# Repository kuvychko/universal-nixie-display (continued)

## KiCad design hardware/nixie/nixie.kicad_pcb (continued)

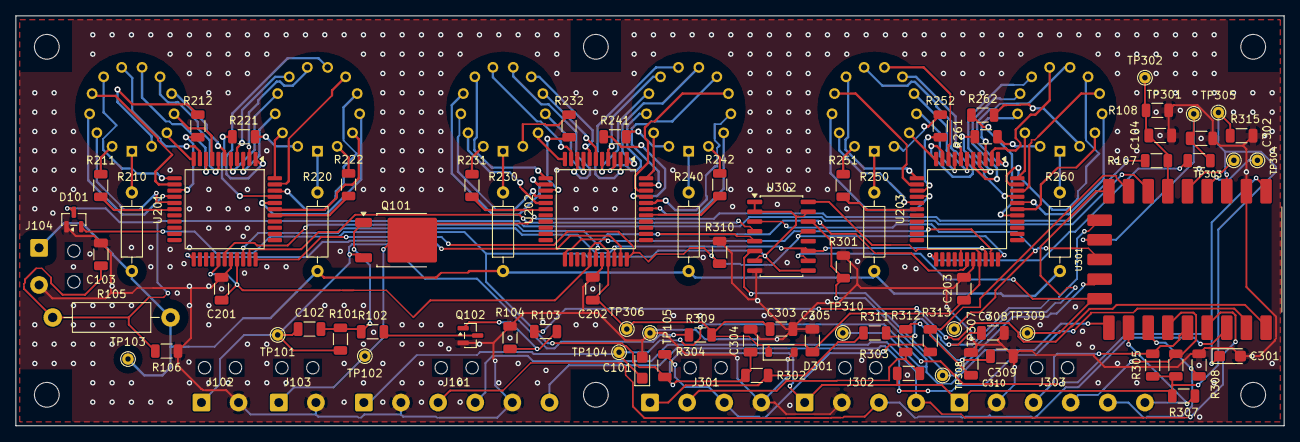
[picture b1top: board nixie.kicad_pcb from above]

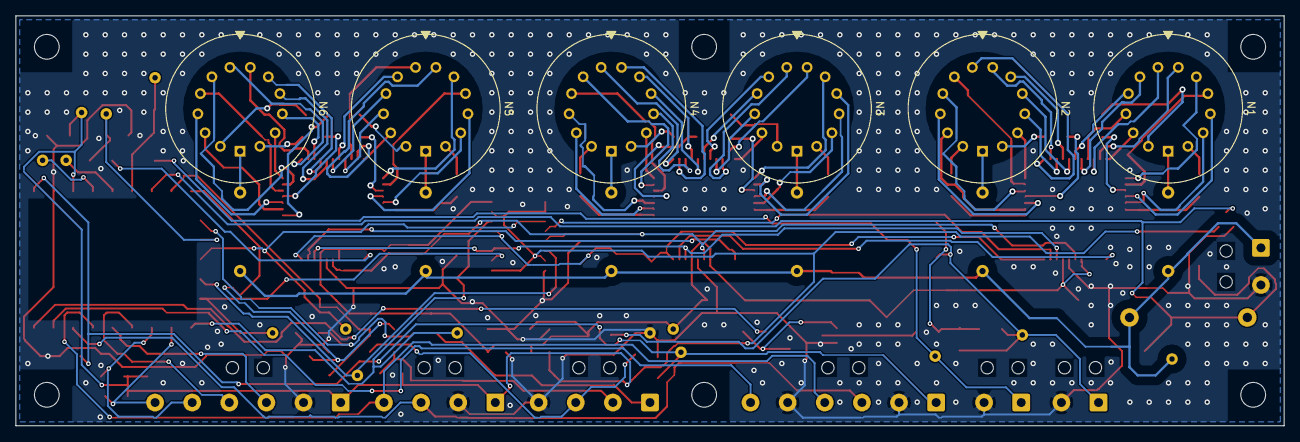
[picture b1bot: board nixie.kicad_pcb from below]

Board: 2 copper layers, 164.0 x 53.0 mm, 106 parts (6 on the bottom side), 130 nets.

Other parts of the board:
H1, H2, H3, H4, H5, H6: MountingHole_3.2mm_M3
TIE_J101, TIE_J102, TIE_J103, TIE_J104, TIE_J301, TIE_J302, TIE_J303: cable tie

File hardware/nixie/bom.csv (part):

Reference,Value,Function,Manufacturer,MPN,Rating,Footprint,Fit
C101,10uF,+5V bulk at the harness landing (user 2026-11-07: as C301),KYOCERA AVX,F911C106MAAAJ6,16 V tantalum,Capacitor_Tantalum_SMD:CP_EIA-3216-18_Kemet-A,
C102,3.3uF,Q101 gate-source: soft turn-on with R101/R102; holds Q101 off on hot-plug,,,25 V X7R,Capacitor_SMD:C_1206_3216Metric,
C103,100nF,NIX_HV_SENSE ADC sampling reservoir (as the dekatron ADC inputs),Yageo,CC1206JPX7R9BB104,50 V X7R,Capacitor_SMD:C_1206_3216Metric,
C104,100nF,NIX12_SENSE ADC sampling reservoir (as the dekatron ADC inputs),Yageo,CC1206JPX7R9BB104,50 V X7R,Capacitor_SMD:C_1206_3216Metric,
C201,0.1uF,U201 VDD bypass,Yageo,CC1206JPX7R9BB104,50 V X7R,Capacitor_SMD:C_1206_3216Metric,
C202,0.1uF,U202 VDD bypass,Yageo,CC1206JPX7R9BB104,50 V X7R,Capacitor_SMD:C_1206_3216Metric,
C203,0.1uF,U203 VDD bypass,Yageo,CC1206JPX7R9BB104,50 V X7R,Capacitor_SMD:C_1206_3216Metric,
C301,10uF,+5V bulk at the module (as dekatron C301),KYOCERA AVX,F911C106MAAAJ6,16 V tantalum,Capacitor_Tantalum_SMD:CP_EIA-3216-18_Kemet-A,
C302,0.1uF,3V3 bypass (as dekatron C302),Yageo,CC1206JPX7R9BB104,50 V X7R,Capacitor_SMD:C_1206_3216Metric,
C303,0.1uF,U302 VDD bypass,Yageo,CC1206JPX7R9BB104,50 V X7R,Capacitor_SMD:C_1206_3216Metric,
C304,0.1uF,U302 VCC bypass,Yageo,CC1206JPX7R9BB104,50 V X7R,Capacitor_SMD:C_1206_3216Metric,
C305,10uF,12 V logic reservoir: shift bursts,,,25 V X7R,Capacitor_SMD:C_1206_3216Metric,
C308,0.01uF,"ENC_A debounce, 0.1 ms with the series 10k (PEC11R suggested filter)",KYOCERA AVX,12063C103JAT2A,25 V X7R,Capacitor_SMD:C_1206_3216Metric,
C309,0.01uF,"ENC_B debounce, 0.1 ms with the series 10k (PEC11R suggested filter)",KYOCERA AVX,12063C103JAT2A,25 V X7R,Capacitor_SMD:C_1206_3216Metric,
C310,0.01uF,"ENC_SW debounce, 0.1 ms with the series 10k (PEC11R suggested filter)",KYOCERA AVX,12063C103JAT2A,25 V X7R,Capacitor_SMD:C_1206_3216Metric,
D101,BAT54S,NIX_HV_SENSE clamp to 3V3 / GND,Taiwan Semiconductor,BAT54S RFG,30 V Schottky pair,Package_TO_SOT_SMD:SOT-23,
D301,MMSZ5243B,12 V logic rail clamp,,MMSZ5243B,"13 V, 500 mW, SOD-123",Diode_SMD:D_SOD-123,
J101,NIX_LV,Harness NIX_LV from the dekatron board (its J302; 5 V behind its ideal diode U104),,,,Connector_Wire:SolderWire-0.5sqmm_1x06_P4.8mm_D0.9mm_OD2.3mm,
J102,12V_IN,"12 V from the dekatron board's NIX_12V (J102, behind its PTC)",,,,Connector_Wire:SolderWire-0.5sqmm_1x02_P4.8mm_D0.9mm_OD2.3mm,
J103,12V_MODULE,Switched 12 V to the Nixie HV module input,,,,Connector_Wire:SolderWire-0.5sqmm_1x02_P4.8mm_D0.9mm_OD2.3mm,
J104,HV_MODULE,Nixie HV module output (~170 V) and its return,,,,Connector_Wire:SolderWire-0.5sqmm_1x02_P4.8mm_D0.9mm_OD2.3mm,
J301,ENCODER,"Harness to the panel-mount encoder (PEC11R): A, B, switch, common C and switch 2",,,,Connector_Wire:SolderWire-0.5sqmm_1x04_P4.8mm_D0.9mm_OD2.3mm,
J302,RTC,Harness to the DS3231 module (ZS-042): jacks on its header by silk name,,,,Connector_Wire:SolderWire-0.5sqmm_1x04_P4.8mm_D0.9mm_OD2.3mm,
J303,WWVB,Harness to the ES100 carrier: jacks on its header by silk name,,,,Connector_Wire:SolderWire-0.5sqmm_1x06_P4.8mm_D0.9mm_OD2.3mm,
N1,IN-14,Tube 1,,IN-14,,nixie:IN-14,
N2,IN-14,Tube 2,,IN-14,,nixie:IN-14,
N3,IN-14,Tube 3,,IN-14,,nixie:IN-14,
N4,IN-14,Tube 4,,IN-14,,nixie:IN-14,
N5,IN-14,Tube 5,,IN-14,,nixie:IN-14,
N6,IN-14,Tube 6,,IN-14,,nixie:IN-14,
Q101,IPD50P04P4L-11,Nixie module 12 V high-side switch with soft start,Infineon,IPD50P04P4L11ATMA2,"-40 V, 17.2 mohm max at VGS -4.5 V, VGS +5/-16 V",Package_TO_SOT_SMD:TO-252-2,
Q102,MMBT3904,Level shifter for Q101's gate,,MMBT3904,40 V NPN,Package_TO_SOT_SMD:SOT-23,
R101,47k,"Q101 gate pull-up: off by default. With R102: VGS -6 V at 12 V, -12 V at the 24 V clamp",,,,Resistor_SMD:R_1206_3216Metric,
R102,47k,Q101 gate series: sets the turn-on ramp with C102,,,,Resistor_SMD:R_1206_3216Metric,
R103,10k,Q102 base (as D8: 3.3 V drive),,,,Resistor_SMD:R_1206_3216Metric,
R104,47k,Q102 base pull-down: switch off while the RP2040 is in reset (D7),,,,Resistor_SMD:R_1206_3216Metric,
R105,1M,"HV monitor divider, upper; bleeder",Yageo,HHV-50FT-52-1M,HHV-50: 0.5 W,Resistor_THT:R_Axial_DIN0411_L9.9mm_D3.6mm_P15.24mm_Horizontal,
R106,12k,"HV monitor divider, lower",Panasonic,ERJ-8ENF1202V,1 %,Resistor_SMD:R_1206_3216Metric,
R107,100k,"+12V_SW sense divider, upper (1.29 V at 12 V)",,,,Resistor_SMD:R_1206_3216Metric,
R108,12k,"+12V_SW sense divider, lower (2.57 V at 24 V)",,,1 %,Resistor_SMD:R_1206_3216Metric,
R210,12k,"Tube 1 anode resistor: (175 V - 145 V) / 2.5 mA, 75 mW",Vishay,MRS25000C1202FRP00,"MRS25: 0.6 W, 350 V, 1 %, 50 ppm/K",Resistor_THT:R_Axial_DIN0207_L6.3mm_D2.5mm_P10.16mm_Horizontal,
R211,150k,"Tube 1 LDP series resistor: starting value, point <= 0.3 mA; check at bring-up",,,,Resistor_SMD:R_1206_3216Metric,
R212,150k,"Tube 1 RDP series resistor: starting value, point <= 0.3 mA; check at bring-up",,,,Resistor_SMD:R_1206_3216Metric,
R220,12k,"Tube 2 anode resistor: (175 V - 145 V) / 2.5 mA, 75 mW",Vishay,MRS25000C1202FRP00,"MRS25: 0.6 W, 350 V, 1 %, 50 ppm/K",Resistor_THT:R_Axial_DIN0207_L6.3mm_D2.5mm_P10.16mm_Horizontal,
R221,150k,"Tube 2 LDP series resistor: starting value, point <= 0.3 mA; check at bring-up",,,,Resistor_SMD:R_1206_3216Metric,
R222,150k,"Tube 2 RDP series resistor: starting value, point <= 0.3 mA; check at bring-up",,,,Resistor_SMD:R_1206_3216Metric,
R230,12k,"Tube 3 anode resistor: (175 V - 145 V) / 2.5 mA, 75 mW",Vishay,MRS25000C1202FRP00,"MRS25: 0.6 W, 350 V, 1 %, 50 ppm/K",Resistor_THT:R_Axial_DIN0207_L6.3mm_D2.5mm_P10.16mm_Horizontal,
R231,150k,"Tube 3 LDP series resistor: starting value, point <= 0.3 mA; check at bring-up",,,,Resistor_SMD:R_1206_3216Metric,
R232,150k,"Tube 3 RDP series resistor: starting value, point <= 0.3 mA; check at bring-up",,,,Resistor_SMD:R_1206_3216Metric,
R240,12k,"Tube 4 anode resistor: (175 V - 145 V) / 2.5 mA, 75 mW",Vishay,MRS25000C1202FRP00,"MRS25: 0.6 W, 350 V, 1 %, 50 ppm/K",Resistor_THT:R_Axial_DIN0207_L6.3mm_D2.5mm_P10.16mm_Horizontal,
R241,150k,"Tube 4 LDP series resistor: starting value, point <= 0.3 mA; check at bring-up",,,,Resistor_SMD:R_1206_3216Metric,
R242,150k,"Tube 4 RDP series resistor: starting value, point <= 0.3 mA; check at bring-up",,,,Resistor_SMD:R_1206_3216Metric,
R250,12k,"Tube 5 anode resistor: (175 V - 145 V) / 2.5 mA, 75 mW",Vishay,MRS25000C1202FRP00,"MRS25: 0.6 W, 350 V, 1 %, 50 ppm/K",Resistor_THT:R_Axial_DIN0207_L6.3mm_D2.5mm_P10.16mm_Horizontal,
R251,150k,"Tube 5 LDP series resistor: starting value, point <= 0.3 mA; check at bring-up",,,,Resistor_SMD:R_1206_3216Metric,
R252,150k,"Tube 5 RDP series resistor: starting value, point <= 0.3 mA; check at bring-up",,,,Resistor_SMD:R_1206_3216Metric,
R260,12k,"Tube 6 anode resistor: (175 V - 145 V) / 2.5 mA, 75 mW",Vishay,MRS25000C1202FRP00,"MRS25: 0.6 W, 350 V, 1 %, 50 ppm/K",Resistor_THT:R_Axial_DIN0207_L6.3mm_D2.5mm_P10.16mm_Horizontal,
R261,150k,"Tube 6 LDP series resistor: starting value, point <= 0.3 mA; check at bring-up",,,,Resistor_SMD:R_1206_3216Metric,
R262,150k,"Tube 6 RDP series resistor: starting value, point <= 0.3 mA; check at bring-up",,,,Resistor_SMD:R_1206_3216Metric,
R301,10k,DRV_BL pull-down: tubes blank while the RP2040 is in reset,,,,Resistor_SMD:R_1206_3216Metric,
R302,10k,ENC_A pull-up (PEC11R suggested filter),,,,Resistor_SMD:R_1206_3216Metric,
R303,10k,ENC_B pull-up (PEC11R suggested filter),,,,Resistor_SMD:R_1206_3216Metric,
R304,10k,ENC_SW pull-up (PEC11R suggested filter),,,,Resistor_SMD:R_1206_3216Metric,
R305,DNP,"WWVB_SDA pull-up: not fitted, 10k on the carrier",,,,Resistor_SMD:R_1206_3216Metric,DNP
R306,DNP,"WWVB_SCL pull-up: not fitted, 10k on the carrier",,,,Resistor_SMD:R_1206_3216Metric,DNP
R307,10k,WWVB_IRQ pull-up (IRQ- is active low),,,,Resistor_SMD:R_1206_3216Metric,
R308,10k,WWVB_EN pull-down: ES100 in shutdown when unplugged or in reset,,,,Resistor_SMD:R_1206_3216Metric,
R309,470,12 V logic rail series resistor: ~0.2 V at ~0.45 mA average; 0.23 W at the 24 V clamp,,,"1206, 0.25 W",Resistor_SMD:R_1206_3216Metric,
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
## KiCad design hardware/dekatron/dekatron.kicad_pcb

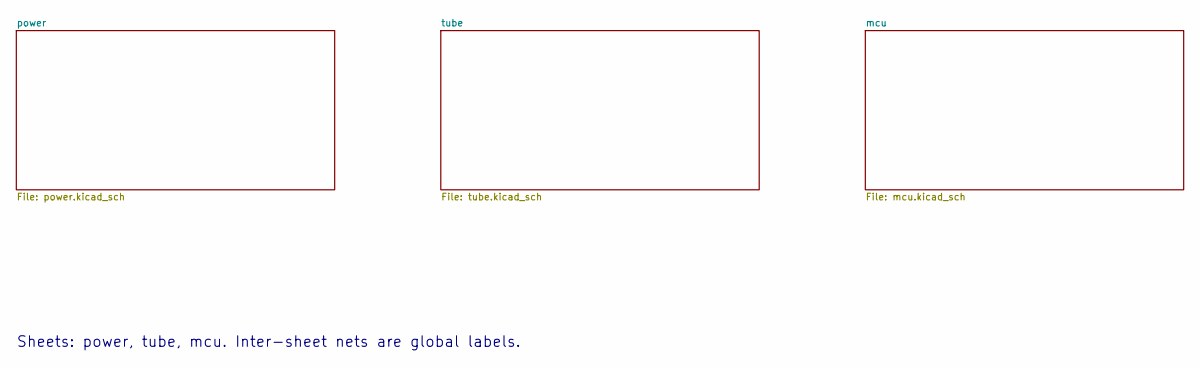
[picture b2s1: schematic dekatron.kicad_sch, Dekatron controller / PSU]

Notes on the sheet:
Sheets: power, tube, mcu. Inter-sheet nets are global labels.

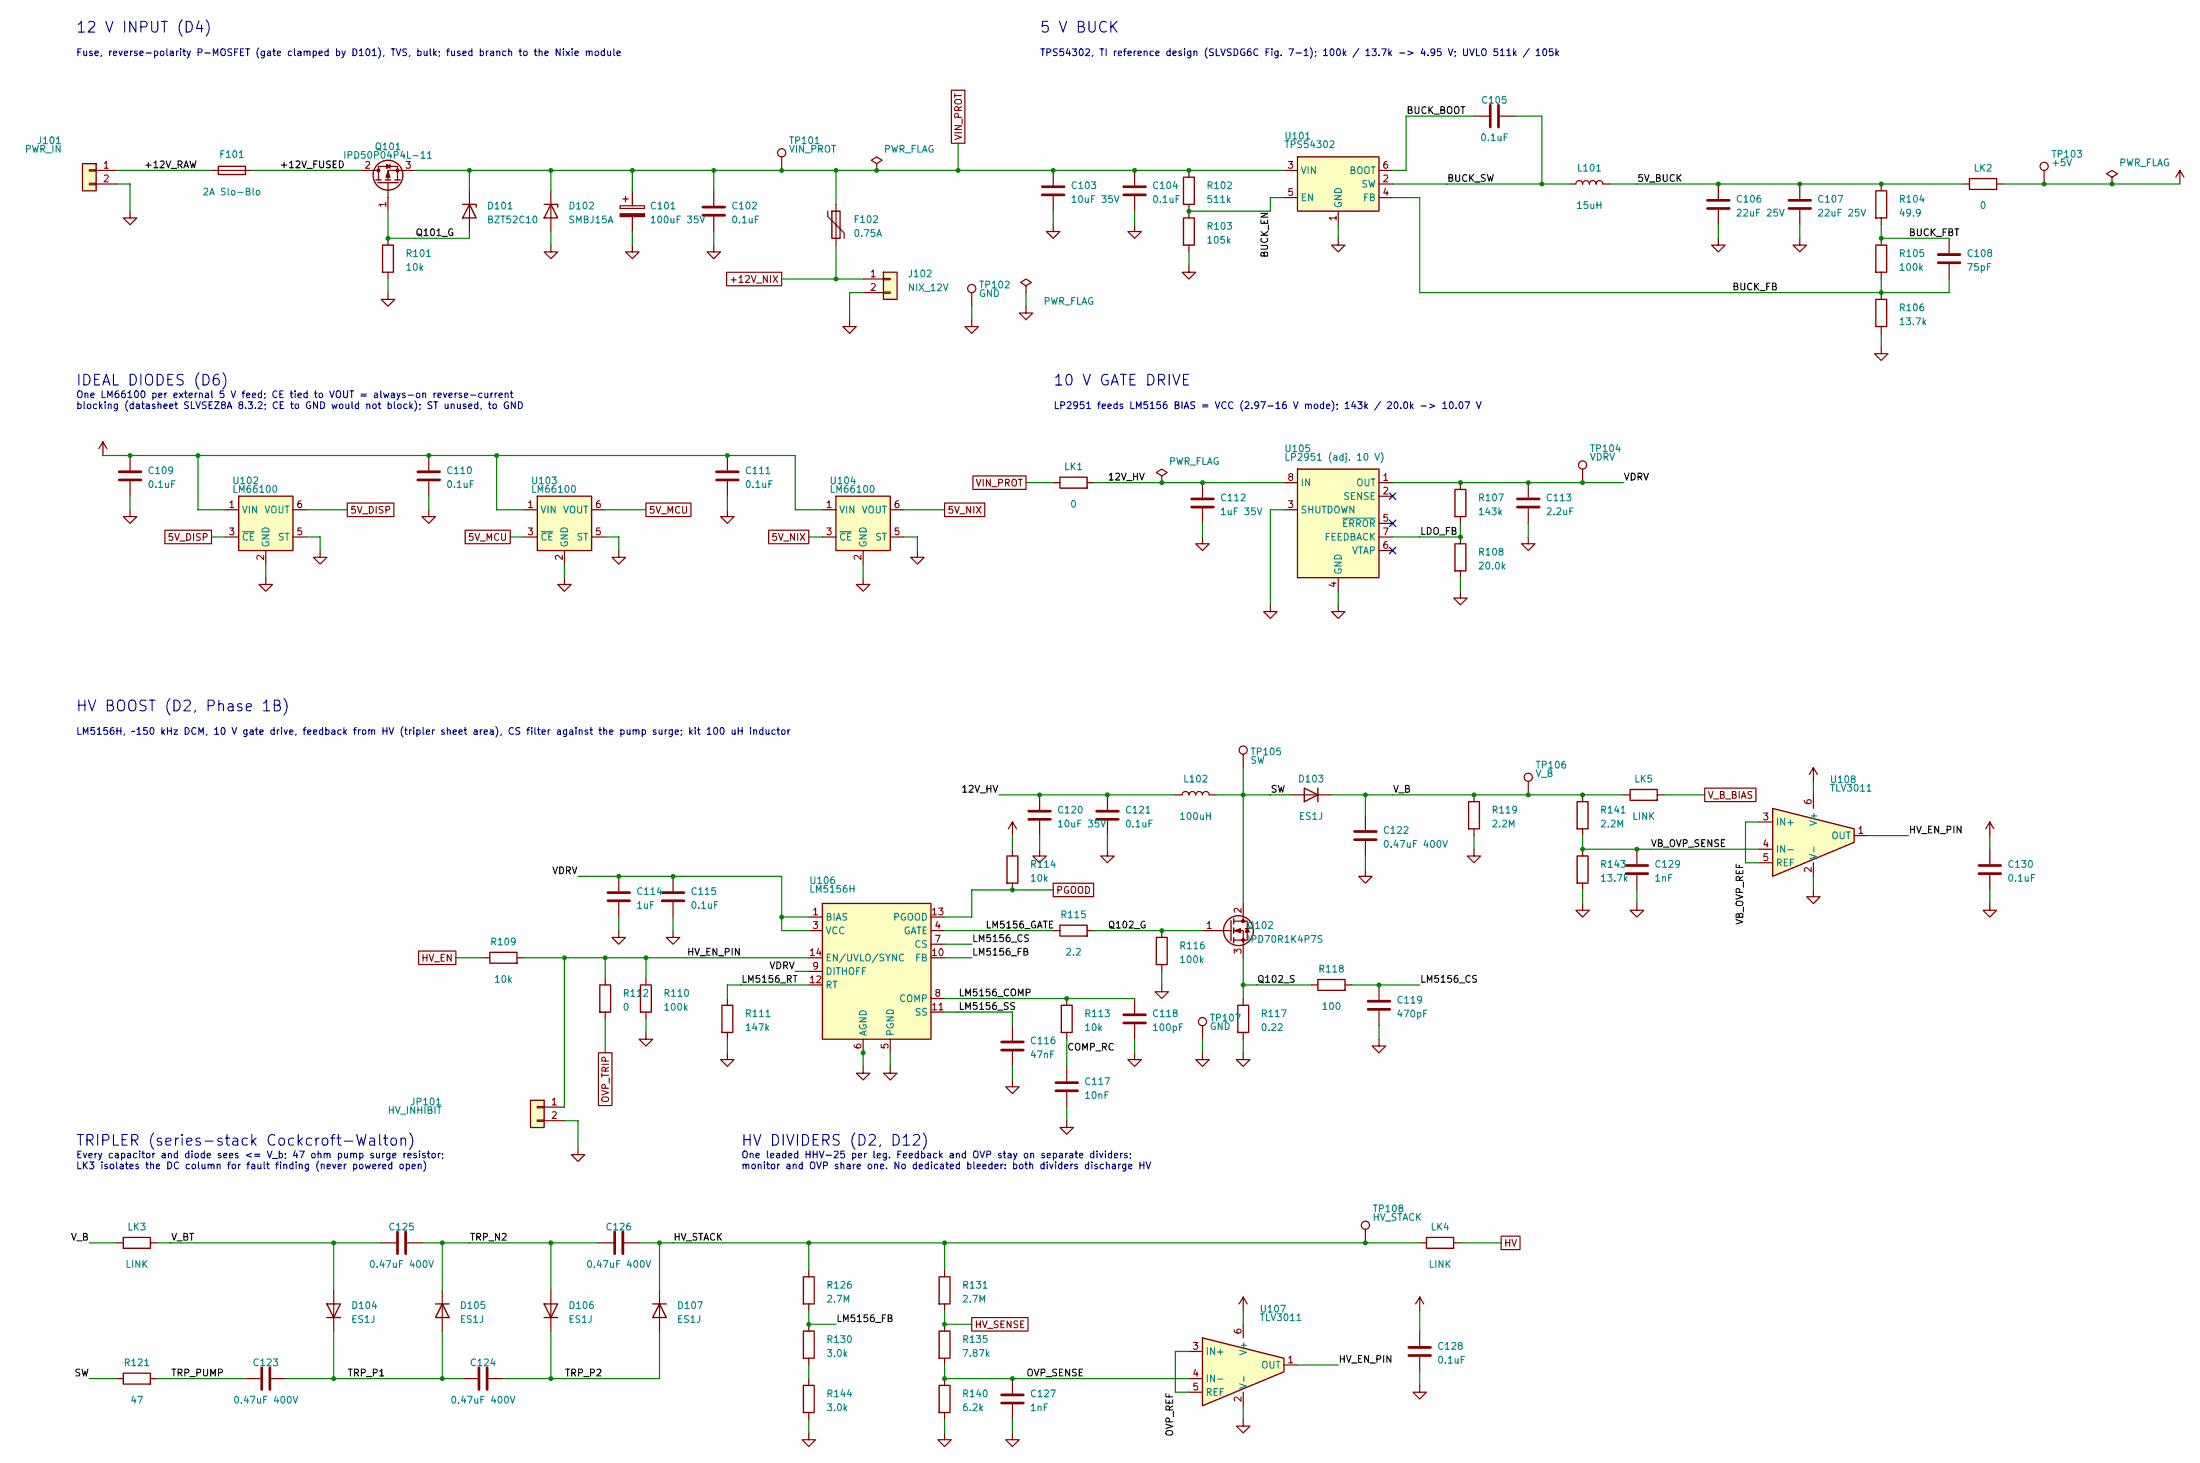
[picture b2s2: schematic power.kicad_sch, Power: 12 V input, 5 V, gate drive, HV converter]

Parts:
C101: 100uF 35V; CP_Elec_6.3x7.7; Rating 35 V, 340 mohm ESR; MPN EEE-FK1V101XP
C102, C104, C109, C110, C111, C115, C121, C128, C130: 0.1uF; C_1206_3216Metric; Rating 50 V X7R; MPN CC1206JPX7R9BB104
C103, C120: 10uF 35V; C_1210_3225Metric; Rating 35 V X7R; MPN CC1210KKX7RGBB106
C105: 0.1uF; C_1206_3216Metric; Rating 25 V X7R; MPN CC1206JPX7R9BB104
C106, C107: 22uF 25V; C_1210_3225Metric; Rating 25 V X7R; MPN MBAST32MSB7226KPNA18
C108: 75pF; C_1206_3216Metric; Rating 50 V C0G; MPN 12065A750JAT2A
C112: 1uF 35V; C_1206_3216Metric; Rating 35 V X7R; MPN 1206DC105MAT2A
C113: 2.2uF; C_1206_3216Metric; Rating 25 V X7R; MPN CS1206KKX7R8BB225
C114: 1uF; C_1206_3216Metric; Rating 25 V X7R; MPN 1206DC105MAT2A
C116: 47nF; C_1206_3216Metric; Rating 25 V X7R; MPN CC1206KRX7R8BB473
C117: 10nF; C_1206_3216Metric; Rating 25 V X7R; MPN 12063C103JAT2A
C118: 100pF; C_1206_3216Metric; Rating 50 V C0G; MPN C1206C101K5GAC7210
C119: 470pF; C_1206_3216Metric; Rating 50 V C0G; MPN 1206B471K500CT
C122, C123, C124, C125, C126: 0.47uF 400V; C_Rect_L18.0mm_W8.0mm_P15.00mm_FKS3_FKP3; Rating 400 V PET film; MPN MKS4G034704F00MSSD
C127, C129: 1nF; C_1206_3216Metric; Rating 50 V C0G; MPN 1206N102K501CT
D101: BZT52C10; D_SOD-123; MPN BZT52C10
D102: SMBJ15A; D_SMB; Rating 15 V standoff, 24.4 V clamp; MPN SMBJ15A
D103, D104, D105, D106, D107: ES1J; D_SMA; Rating 600 V, 1 A, 35 ns; MPN ES1J
F101: 2A Slo-Blo; Fuse_1206_3216Metric; Rating 2 A, 63 V, I2t 0.506 A2s; MPN 0468002.NRHF
F102: 0.75A; Fuse_1812_4532Metric; Rating 0.75 A hold, 33 V; MPN 1812L075/33DR
J101: PWR_IN; SolderWire-0.5sqmm_1x02_P4.8mm_D0.9mm_OD2.3mm
J102: NIX_12V; SolderWire-0.5sqmm_1x02_P4.8mm_D0.9mm_OD2.3mm
JP101: HV_INHIBIT; PinHeader_1x02_P2.54mm_Vertical
L101: 15uH; L_Radial_D6.0mm_P4.00mm; Rating Rated 1.31 A; limits the 5 V rail to ~1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; MPN (kit, 6 x 8 mm radial)
L102: 100uH; L_Radial_D6.0mm_P4.00mm; Rating Rated 0.71 A, DCR 0.35 ohm, 4 mm pitch; MPN (kit, 6 x 8 mm radial)
LK1, LK2: 0; R_1206_3216Metric
LK3, LK4, LK5: LINK; R_Axial_DIN0207_L6.3mm_D2.5mm_P7.62mm_Horizontal
Q101: IPD50P04P4L-11; TO-252-2; Rating -40 V, 10.6 mohm, 200 A pulsed, VGS +5/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; MPN IPD50P04P4L11ATMA2
Q102: IPD70R1K4P7S; TO-252-2; Rating 700 V, 1.4 ohm at 10 V, VGS +/-16 V; MPN IPD70R1K4P7SAUMA1
R101, R109, R113, R114: 10k; R_1206_3216Metric
R102: 511k; R_1206_3216Metric; MPN RT1206FRE07511KL
R103: 105k; R_1206_3216Metric; MPN CR1206-FX-1053ELF
R104: 49.9; R_1206_3216Metric; MPN RCC120649R9FKEA
R105, R110, R116: 100k; R_1206_3216Metric
R106, R143: 13.7k; R_1206_3216Metric; Rating 1 %; MPN CR1206-FX-1372ELF
R107: 143k; R_1206_3216Metric; Rating 1 %; MPN CR1206-FX-1433ELF
R108: 20.0k; R_1206_3216Metric; Rating 1 %; MPN RK73H2BLTD2002F
R111: 147k; R_1206_3216Metric; MPN CRCW1206147KFKTA
R112: 0; R_1206_3216Metric
R115: 2.2; R_1206_3216Metric
R117: 0.22; R_1206_3216Metric; Rating 1 %, >= 0.25 W; MPN RNCL1206FTR220
R118: 100; R_1206_3216Metric
R119, R141: 2.2M; R_Axial_DIN0207_L6.3mm_D2.5mm_P10.16mm_Horizontal; Rating HHV-25: 0.25 W, 1600 V DC, 1 %, 200 ppm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; MPN HHV-25FT-52-2M2
R121: 47; R_1206_3216Metric
R126, R131: 2.7M; R_Axial_DIN0207_L6.3mm_D2.5mm_P10.16mm_Horizontal; Rating HHV-25: 0.25 W, 1600 V DC, 1 %, 200 ppm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; MPN HHV-25FR-52-2M7
R130, R144: 3.0k; R_0805_2012Metric; Rating 1 %; MPN 292-3.0K-RC
R135: 7.87k; R_1206_3216Metric; Rating 1 %; MPN ERJ-8ENF7871V
R140: 6.2k; R_1206_3216Metric; Rating 1 %; MPN CRCW12066K20FKEAC
TP101: VIN_PROT; TestPoint_THTPad_D1.5mm_Drill0.7mm
TP102, TP107: GND; TestPoint_THTPad_D1.5mm_Drill0.7mm
TP103: +5V; TestPoint_THTPad_D1.5mm_Drill0.7mm
TP104: VDRV; TestPoint_THTPad_D1.5mm_Drill0.7mm
TP105: SW; TestPoint_THTPad_D1.5mm_Drill0.7mm
TP106: V_B; TestPoint_THTPad_D1.5mm_Drill0.7mm
TP108: HV_STACK; TestPoint_THTPad_D1.5mm_Drill0.7mm
U101: TPS54302; SOT-23-6; Rating 4.5-28 V, 3 A, 400 kHz; MPN TPS54302DDCR
U102, U103, U104: LM66100; SOT-363_SC-70-6; Rating 1.5 A, reverse blocking; MPN LM66100DCKR
U105: LP2951 (adj. 10 V); SOIC-8_3.9x4.9mm_P1.27mm; Rating 30 V in, 100 mA; MPN LP2951ACDR2G
U106: LM5156H; Texas_HTSSOP-14-1EP_4.4x5mm_P0.65mm_EP3.4x5mm_Mask3.155x3.2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; Rating HTSSOP-14 exposed pad; MPN LM5156HPWPR
U107, U108: TLV3011; SOT-23-6; Rating 1.242 V ref; MPN TLV3011AIDBVR

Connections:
5V_DISP: U102.3 (~CE), U102.6 (VOUT); also elsewhere on the board
5V_MCU: U103.3 (~CE), U103.6 (VOUT); also elsewhere on the board
5V_NIX: U104.3 (~CE), U104.6 (VOUT); also elsewhere on the board
+3V3: R114.1; also elsewhere on the board
+5V: C109.1, C110.1, C111.1, C128.1, C130.1, LK2.2, TP103.1, U102.1 (VIN), U103.1 (VIN), U104.1 (VIN), U107.6 (V+), U108.6 (V+)
+12V_NIX: F102.2, J102.1
/power/5V_BUCK: C106.1, C107.1, L101.2, LK2.1, R104.1
/power/12V_HV: C112.1, C120.1, C121.1, L102.1, LK1.2, U105.8 (IN)
/power/+12V_FUSED: F101.2, Q101.2 (D)
/power/+12V_RAW: F101.1, J101.1
/power/BUCK_BOOT: C105.1, U101.6 (BOOT)
/power/BUCK_EN: R102.2, R103.1, U101.5 (EN)
/power/BUCK_FB: C108.2, R105.2, R106.1, U101.4 (FB)
/power/BUCK_FBT: C108.1, R104.2, R105.1
/power/BUCK_SW: C105.2, L101.1, U101.2 (SW)
/power/COMP_RC: C117.1, R113.2
/power/HV_EN_PIN: JP101.1, R109.2, R110.1, R112.1, U106.14 (EN/UVLO/SYNC), U107.1 (OUT), U108.1 (OUT)
/power/HV_STACK: C126.2, D107.1 (K), LK4.1, R126.1, R131.1, TP108.1
/power/LDO_FB: R107.2, R108.1, U105.7 (FEEDBACK)
/power/LM5156_COMP: C118.1, R113.1, U106.8 (COMP)
/power/LM5156_CS: C119.1, R118.2, U106.7 (CS)
/power/LM5156_FB: R126.2, R130.1, U106.10 (FB)
/power/LM5156_GATE: R115.1, U106.4 (GATE)
/power/LM5156_RT: R111.1, U106.12 (RT)
/power/LM5156_SS: C116.1, U106.11 (SS)
/power/OVP_REF: U107.3 (IN+), U107.5 (REF)
/power/OVP_SENSE: C127.1, R135.2, R140.1, U107.4 (IN-)
/power/Q101_G: D101.2 (A), Q101.1 (G), R101.1
/power/Q102_G: Q102.1 (G), R115.2, R116.1
/power/Q102_S: Q102.3 (S), R117.1, R118.1
/power/SW: D103.2 (A), L102.2, Q102.2 (D), R121.1, TP105.1
/power/TRP_N2: C125.2, C126.1, D105.1 (K), D106.2 (A)
/power/TRP_P1: C123.2, C124.1, D104.1 (K), D105.2 (A)
/power/TRP_P2: C124.2, D106.1 (K), D107.2 (A)
/power/TRP_PUMP: C123.1, R121.2
/power/VB_OVP_REF: U108.3 (IN+), U108.5 (REF)
/power/VB_OVP_SENSE: C129.1, R141.2, R143.1, U108.4 (IN-)
/power/VDRV: C113.1, C114.1, C115.1, R107.1, TP104.1, U105.1 (OUT), U106.1 (BIAS), U106.3 (VCC), U106.9 (DITHOFF)
/power/V_B: C122.1, D103.1 (K), LK3.1, LK5.1, R119.1, R141.1, TP106.1
/power/V_BT: C125.1, D104.2 (A), LK3.2
GND: C101.2, C102.2, C103.2, C104.2, C106.2, C107.2, C109.2, C110.2, C111.2, C112.2, C113.2, C114.2, C115.2, C116.2, C117.2, C118.2, C119.2, C120.2, C121.2, C122.2, C127.2, C128.2, C129.2, C130.2, D102.2 (A), J101.2, J102.2, JP101.2, R101.2, R103.2, R106.2, R108.2, R110.2, R111.2, R116.2, R117.2, R119.2, R140.2, R143.2, R144.2, TP102.1, TP107.1, U101.1 (GND), U102.2 (GND), U102.5 (ST), U103.2 (GND), U103.5 (ST), U104.2 (GND), U104.5 (ST), U105.3 (SHUTDOWN), U105.4 (GND), U106.5 (PGND), U106.6 (AGND), U106.15 (AGND), U107.2 (V-), U108.2 (V-); also elsewhere on the board
HV: LK4.2; also elsewhere on the board
HV_EN: R109.1; also elsewhere on the board
HV_SENSE: R131.2, R135.1; also elsewhere on the board
unnamed: R130.2, R144.1
OVP_TRIP: R112.2; also elsewhere on the board
PGOOD: R114.2, U106.13 (PGOOD); also elsewhere on the board
VIN_PROT: C101.1, C102.1, C103.1, C104.1, D101.1 (K), D102.1 (K), F102.1, LK1.1, Q101.3 (S), R102.1, TP101.1, U101.3 (VIN); also elsewhere on the board
V_B_BIAS: LK5.2; also elsewhere on the board

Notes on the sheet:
12 V INPUT (D4)
Fuse, reverse-polarity P-MOSFET (gate clamped by D101), TVS, bulk; fused branch to the Nixie module
5 V BUCK
TPS54302, TI reference design (SLVSDG6C Fig. 7-1); 100k / 13.7k -> 4.95 V; UVLO 511k / 105k
IDEAL DIODES (D6)
One LM66100 per external 5 V feed; CE tied to VOUT = always-on reverse-current blocking (datasheet SLVSEZ8A 8.3.2; CE to GND would not block); ST unused, to GND
10 V GATE DRIVE
LP2951 feeds LM5156 BIAS = VCC (2.97-16 V mode); 143k / 20.0k -> 10.07 V
HV BOOST (D2, Phase 1B)
LM5156H, ~150 kHz DCM, 10 V gate drive, feedback from HV (tripler sheet area), CS filter against the pump surge; kit 100 uH inductor
TRIPLER (series-stack Cockcroft-Walton)
Every capacitor and diode sees <= V_b; 47 ohm pump surge resistor; LK3 isolates the DC column for fault finding (never powered open)
HV DIVIDERS (D2, D12)
One leaded HHV-25 per leg. Feedback and OVP stay on separate dividers; monitor and OVP share one. No dedicated bleeder: both dividers discharge HV

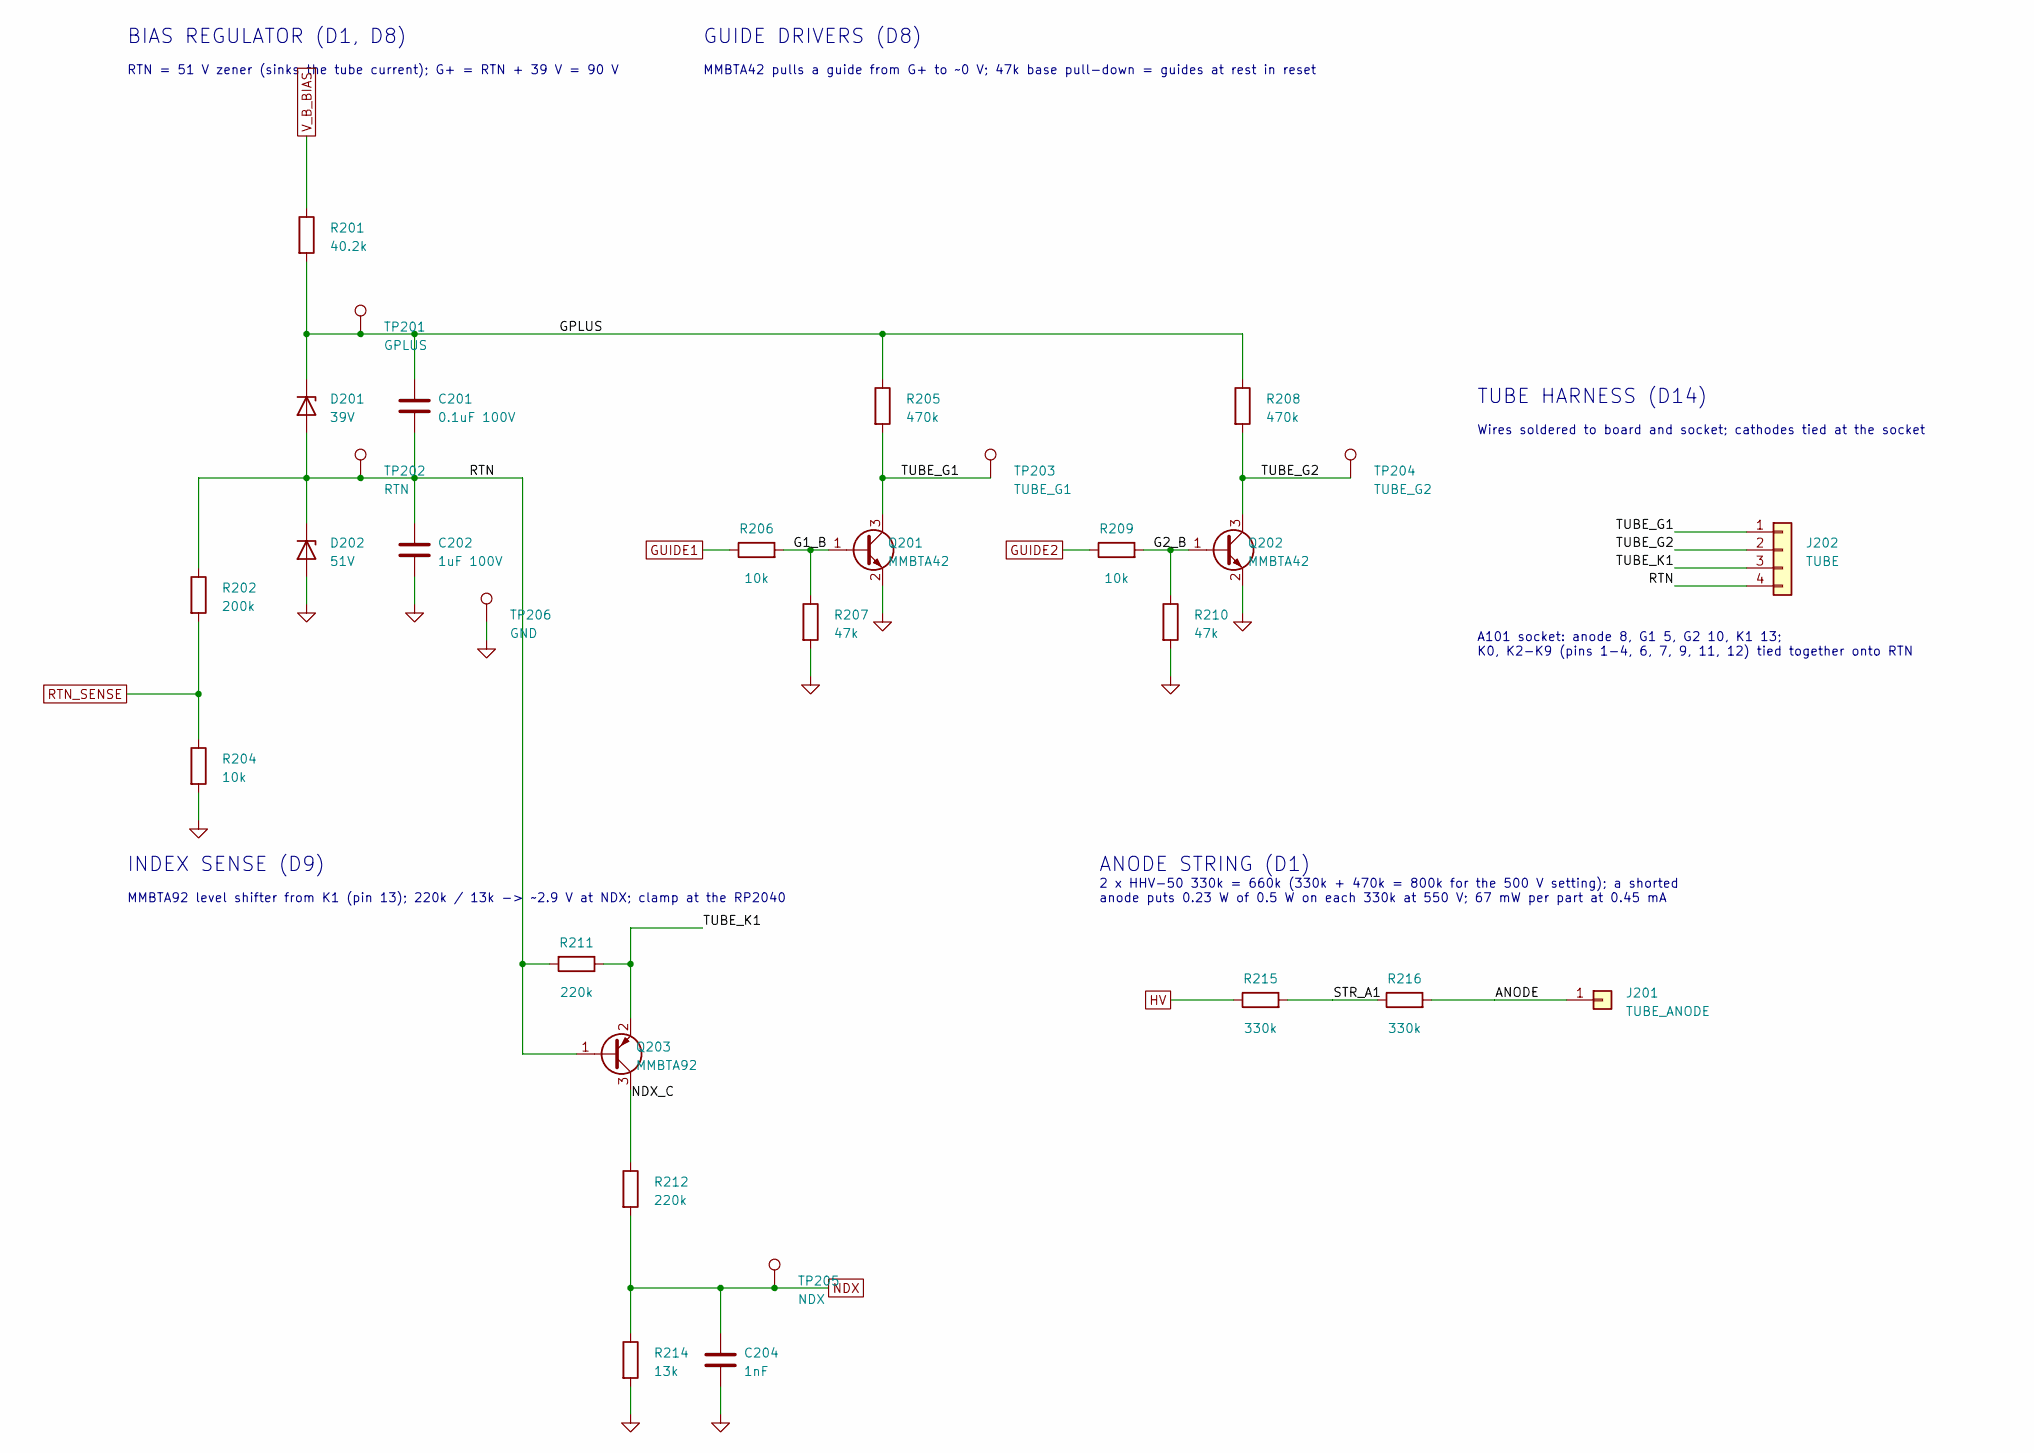
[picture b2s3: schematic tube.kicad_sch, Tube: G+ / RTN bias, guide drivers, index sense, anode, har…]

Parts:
C201: 0.1uF 100V; C_1206_3216Metric; Rating 100 V X7R; MPN AC1206KKX7R0BB104
C202: 1uF 100V; C_1206_3216Metric; Rating 100 V X7R; MPN C1206C105M1RACAUTO
C204: 1nF; C_1206_3216Metric; Rating 50 V C0G; MPN 1206N102K501CT
D201: 39V; D_SOD-123; Rating 39 V, 500 mW; MPN MMSZ5259BH RHG
D202: 51V; D_SOD-123; Rating 51 V, 500 mW; MPN MMSZ5262BT1G
J201: TUBE_ANODE; SolderWire-0.5sqmm_1x01_D0.9mm_OD2.3mm
J202: TUBE; SolderWire-0.5sqmm_1x04_P4.8mm_D0.9mm_OD2.3mm
Q201, Q202: MMBTA42; SOT-23; Rating 300 V NPN; MPN MMBTA42
Q203: MMBTA92; SOT-23; Rating 300 V PNP; MPN MMBTA92
R201: 40.2k; R_Axial_DIN0207_L6.3mm_D2.5mm_P10.16mm_Horizontal; Rating MRS25: 0.6 W, 350 V, 1 %, 50 ppm/K; MPN MRS25000C4022FCT00
R202: 200k; R_Axial_DIN0207_L6.3mm_D2.5mm_P10.16mm_Horizontal; Rating HHV-25: 0.25 W, 1600 V DC, 1 %, 200 ppm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; MPN HHV-25FR-52-200K
R204: 10k; R_1206_3216Metric; Rating 1 %
R205, R208: 470k; R_1206_3216Metric
R206, R209: 10k; R_1206_3216Metric
R207, R210: 47k; R_1206_3216Metric
R211: 220k; R_1206_3216Metric
R212: 220k; R_Axial_DIN0207_L6.3mm_D2.5mm_P10.16mm_Horizontal; Rating HHV-25: 0.25 W, 1600 V DC, 1 %, 200 ppm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; MPN HHV-25FR-52-220K
R214: 13k; R_1206_3216Metric; Rating 1 %; MPN CR1206-FX-1302ELF
R215, R216: 330k; R_Axial_DIN0411_L9.9mm_D3.6mm_P15.24mm_Horizontal; Rating HHV-50: 0.5 W, 3500 V DC, 1 %, 200 ppm/K; MPN HHV-50FR-52-330K
TP201: GPLUS; TestPoint_THTPad_D1.5mm_Drill0.7mm
TP202: RTN; TestPoint_THTPad_D1.5mm_Drill0.7mm
TP203: TUBE_G1; TestPoint_THTPad_D1.5mm_Drill0.7mm
TP204: TUBE_G2; TestPoint_THTPad_D1.5mm_Drill0.7mm
TP205: NDX; TestPoint_THTPad_D1.5mm_Drill0.7mm
TP206: GND; TestPoint_THTPad_D1.5mm_Drill0.7mm

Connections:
/tube/ANODE: J201.1, R216.2
/tube/G1_B: Q201.1 (B), R206.2, R207.1
/tube/G2_B: Q202.1 (B), R209.2, R210.1
/tube/GPLUS: C201.1, D201.1 (K), R201.2, R205.1, R208.1, TP201.1
/tube/NDX_C: Q203.3 (C), R212.1
/tube/RTN: C201.2, C202.1, D201.2 (A), D202.1 (K), J202.4, Q203.1 (B), R202.1, R211.2, TP202.1
/tube/STR_A1: R215.2, R216.1
/tube/TUBE_G1: J202.1, Q201.3 (C), R205.2, TP203.1
/tube/TUBE_G2: J202.2, Q202.3 (C), R208.2, TP204.1
/tube/TUBE_K1: J202.3, Q203.2 (E), R211.1
GND: C202.2, C204.2, D202.2 (A), Q201.2 (E), Q202.2 (E), R204.2, R207.2, R210.2, R214.2, TP206.1; also elsewhere on the board
GUIDE1: R206.1; also elsewhere on the board
GUIDE2: R209.1; also elsewhere on the board
HV: R215.1; also elsewhere on the board
NDX: C204.1, R212.2, R214.1, TP205.1; also elsewhere on the board
RTN_SENSE: R202.2, R204.1; also elsewhere on the board
V_B_BIAS: R201.1; also elsewhere on the board

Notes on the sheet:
BIAS REGULATOR (D1, D8)
RTN = 51 V zener (sinks the tube current); G+ = RTN + 39 V = 90 V
GUIDE DRIVERS (D8)
MMBTA42 pulls a guide from G+ to ~0 V; 47k base pull-down = guides at rest in reset
INDEX SENSE (D9)
MMBTA92 level shifter from K1 (pin 13); 220k / 13k -> ~2.9 V at NDX; clamp at the RP2040
ANODE STRING (D1)
2 x HHV-50 330k = 660k (330k + 470k = 800k for the 500 V setting); a shorted anode puts 0.23 W of 0.5 W on each 330k at 550 V; 67 mW per part at 0.45 mA
TUBE HARNESS (D14)
Wires soldered to board and socket; cathodes tied at the socket
A101 socket: anode 8, G1 5, G2 10, K1 13; K0, K2-K9 (pins 1-4, 6, 7, 9, 11, 12) tied together onto RTN
